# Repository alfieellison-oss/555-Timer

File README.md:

# Alfie's Blinky Project

Hello! This is my repo for a Blinky project! This was made as abit of fun while leanring to use 555 timing IC's in larger circuits..

## Features

- 10 LED's'

- A 555 IC
 
- A 4017 I/O expander IC

## PCB

Here are pictures of my pcb:

| \*\*Schematic\*\* | \*\*PCB\*\* |

|---------------|---------|
=======

## Notes

- Making this is only my second time usign KiCAD so forgive any mistakes that have been made. this was my first time importng images into KiCAD and the only time i have made a non-rectangular PCB shape.

## BOM

| Ref    | Component             | Value / Description         | Footprint               | Qty |
| ------ | --------------------- | --------------------------- | ----------------------- | --- |
| C1     | Capacitor             | 0.01 µF (10 nF)             | Disc, THT, 5.0 mm pitch | 1   |
| C2     | Capacitor             | 1 µF                        | Disc, THT, 5.0 mm pitch | 1   |
| D1–D10 | LED                   | Standard 5 mm LED           | LED_THT:LED_D5.0mm      | 10  |
| R1     | Resistor              | 470 Ω                       | Axial THT, 7.62 mm      | 1   |
| R2     | Resistor              | 1 kΩ                        | Axial THT, 7.62 mm      | 1   |
| RV1    | Potentiometer         | 50 kΩ Trimmer               | Bourns 3296W (Vertical) | 1   |
| U1     | Timer IC              | NE555P                      | DIP-8                   | 1   |
| U2     | Decade Counter IC     | CD4017                      | DIP-16                  | 1   |
| PCB    | Printed Circuit Board | Custom PCB for this project | —                       | 1   |

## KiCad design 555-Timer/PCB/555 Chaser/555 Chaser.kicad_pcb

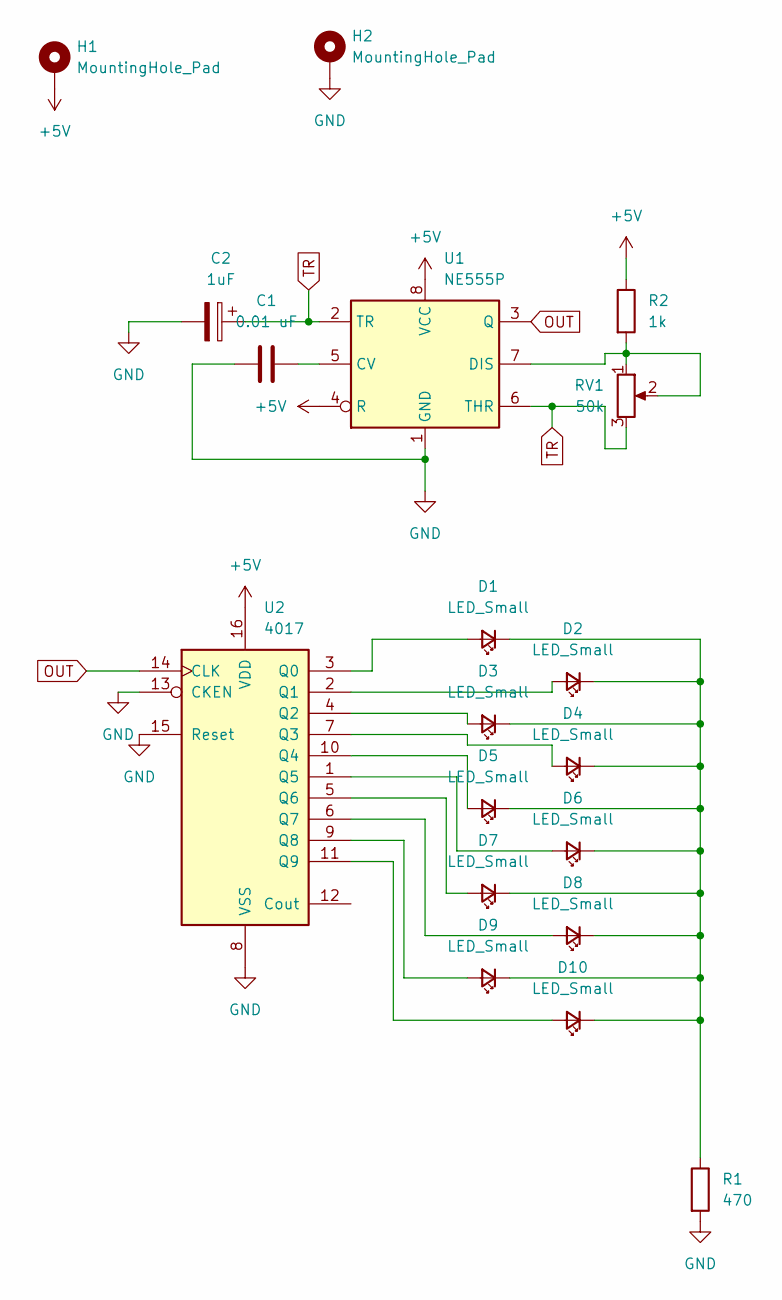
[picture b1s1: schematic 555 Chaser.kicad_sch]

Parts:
C1: 0.01 uF; C_Disc_D5.1mm_W3.2mm_P5.00mm
C2: 1uF; C_Disc_D7.5mm_W5.0mm_P5.00mm
D1, D2, D3, D4, D5, D6, D7, D8, D9, D10: LED_Small; LED_D5.0mm
H1, H2: MountingHole_Pad; MountingHole_3.2mm_M3_Pad
R1: 470; R_Axial_DIN0207_L6.3mm_D2.5mm_P7.62mm_Horizontal
R2: 1k; R_Axial_DIN0207_L6.3mm_D2.5mm_P7.62mm_Horizontal
RV1: 50k; Potentiometer_Bourns_3296W_Vertical
U1: NE555P; DIP-8_W7.62mm
U2: 4017; N16

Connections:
+5V: H1.1, R2.1, U1.4 (R), U1.8 (VCC), U2.16 (VDD)
GND: C1.1, C2.2, H2.1, R1.2, U1.1 (GND), U2.8 (VSS), U2.13 (CKEN), U2.15 (Reset)
unnamed: D1.2 (A), U2.3 (Q0)
unnamed: D1.1 (K), D2.1 (K), D3.1 (K), D4.1 (K), D5.1 (K), D6.1 (K), D7.1 (K), D8.1 (K), D9.1 (K), D10.1 (K), R1.1
unnamed: D2.2 (A), U2.2 (Q1)
unnamed: D3.2 (A), U2.4 (Q2)
unnamed: D4.2 (A), U2.7 (Q3)
unnamed: D5.2 (A), U2.10 (Q4)
unnamed: D6.2 (A), U2.1 (Q5)
unnamed: D7.2 (A), U2.5 (Q6)
unnamed: D8.2 (A), U2.6 (Q7)
unnamed: D9.2 (A), U2.9 (Q8)
unnamed: D10.2 (A), U2.11 (Q9)
unnamed: C1.2, U1.5 (CV)
unnamed: R2.2, RV1.1, RV1.2, U1.7 (DIS)
OUT: U1.3 (Q), U2.14 (CLK)
TR: C2.1, RV1.3, U1.2 (TR), U1.6 (THR)

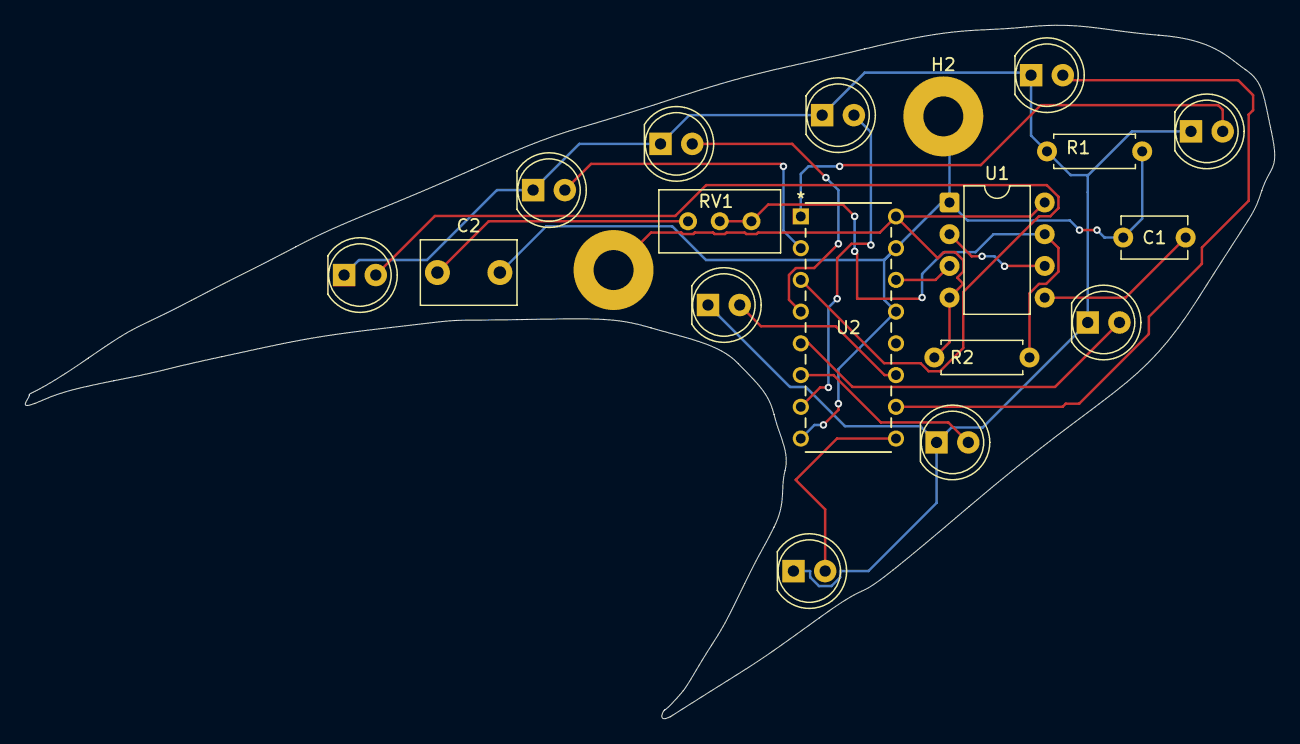
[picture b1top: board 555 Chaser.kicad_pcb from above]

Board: 2 copper layers, 100.0 x 55.5 mm, 19 parts (0 on the bottom side), 17 nets.

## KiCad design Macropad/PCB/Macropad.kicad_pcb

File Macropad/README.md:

\# Alfie's CAD Macropad

Hello! This is my submission for hackpad! This was made with the intention to streamline common cad commands in Autodesk software.

\## Features

\- 5 keyboard switches

\- A rotary encoder with button function
 
\- kmk firmware

\## PCB

Here are pictures of my pcb:

| \*\*Schematic\*\* | \*\*PCB\*\* |

|---------------|---------|
=======

\## Firmware

I wrote the firmware using kmk, you can see it inside the repo. 

\## Notes

Making the  pad was my first time using KiCAD, but hopefully wont be the last. I experimented a fair bit with my trace routing before i came up with a layput that i was moderately happy with.

\## BOM

\- 1 SEEEDUINO XIAO RP2040

\- 5x Cherry MX Switches (Button_Switch_Keyboard:SW_Cherry_MX_1.00u_PCB)

\- 1 Rotary_Encoder:RotaryEncoder_Alps_EC11E-Switch_Vertical_H20mm_CircularMountingHoles

\- 2x SK6812MINI  LED_SMD:LED_SK6812MINI_PLCC4_3.5x3.5mm_P1.75mm

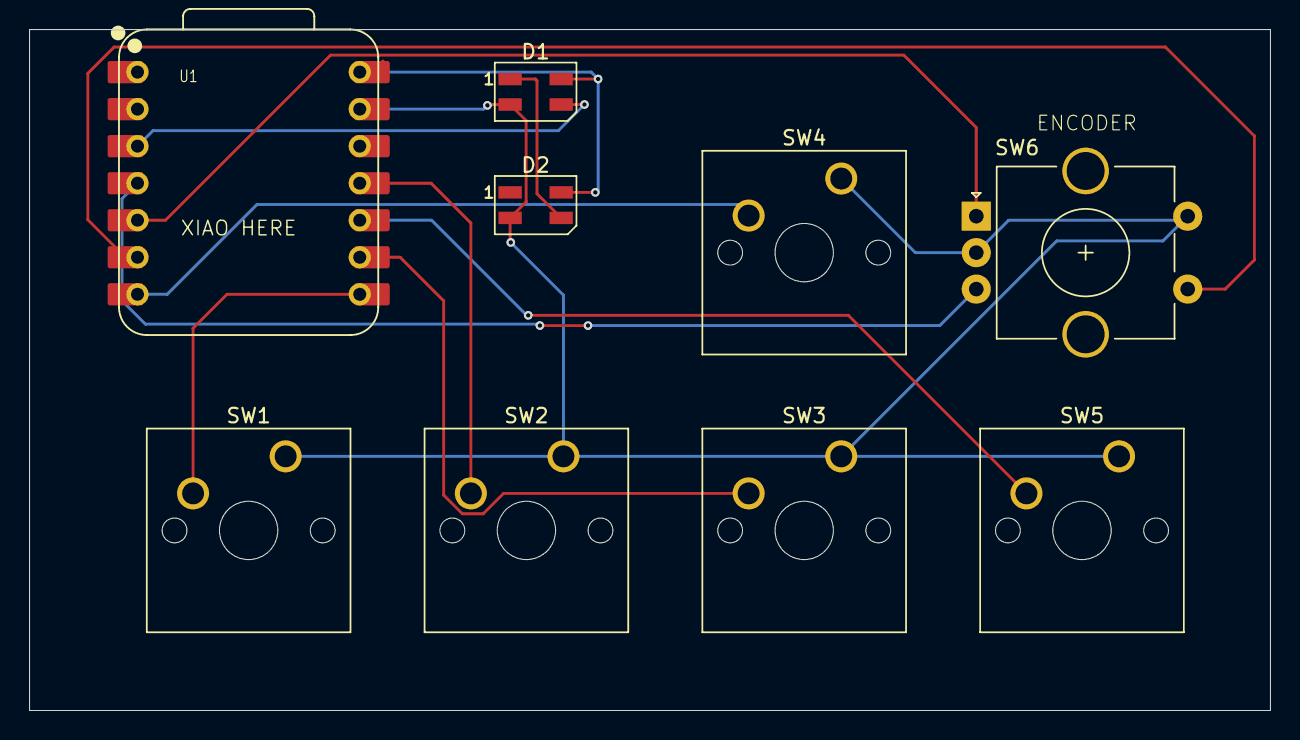
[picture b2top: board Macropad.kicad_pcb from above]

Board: 2 copper layers, 85.1 x 46.7 mm, 9 parts (0 on the bottom side), 12 nets.

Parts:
D1, D2: SK6812MINI; LED_SK6812MINI_PLCC4_3.5x3.5mm_P1.75mm
SW1, SW2, SW3, SW4, SW5: SW_Push; SW_Cherry_MX_1.00u_PCB
SW6: RotaryEncoder_Switch; RotaryEncoder_Alps_EC11E-Switch_Vertical_H20mm_CircularMoun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
U1: XIAO-RP2040-DIP

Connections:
+5V: D1.4 (VDD), D2.4 (VDD), U1.14 (VBUS)
GND: D1.2 (VSS), D2.2 (VSS), SW1.1, SW2.1, SW3.1, SW4.1, SW5.1, SW6.C, SW6.S2, U1.13 (GND)
unnamed: D1.3 (DIN), U1.3 (GPIO28/ADC2/A2)
unnamed: D1.1 (DOUT), D2.3 (DIN)
unnamed: SW4.2, U1.7 (GPIO0/TX)
unnamed: SW1.2, U1.8 (GPIO1/RX)
unnamed: SW3.2, U1.9 (GPIO2/SCK)
unnamed: SW2.2, U1.11 (GPIO3/MOSI)
unnamed: SW5.2, U1.10 (GPIO4/MISO)
unnamed: SW6.A, U1.5 (GPIO6/SDA)
unnamed: SW6.S1, U1.6 (GPIO7/SCL)
unnamed: SW6.B, U1.4 (GPIO29/ADC3/A3)

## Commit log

2025-12-15 Cleaned up the files and organised them into folders (CAD, PCD, Firmware).
2025-12-15 updating README.md
2025-12-19 Formatting README.md
2025-12-19 Added CAD screenshots to README.md
2025-12-19 Added CAD screenshots to Images folder
2025-12-25 Images of schematic and PCB
2025-12-25 Adding README.md
2025-12-25 Updating File Structure
